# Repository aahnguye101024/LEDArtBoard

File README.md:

# LEDArtBoard
This project is an ESP32 that can control a huge array of leds in order to generate pixel art. With a single 12V input, you can power on an ESP32 and huge array of leds (at very low current draw for each led). It was intended as a gift for a friend, where I could upload an array of values with specific RGB codes to display that color in that specific led location on the array. It was also to test JLCPCB's new at the time feature to assemble PCBs for a super low cost.

# Main Board

# LED Board

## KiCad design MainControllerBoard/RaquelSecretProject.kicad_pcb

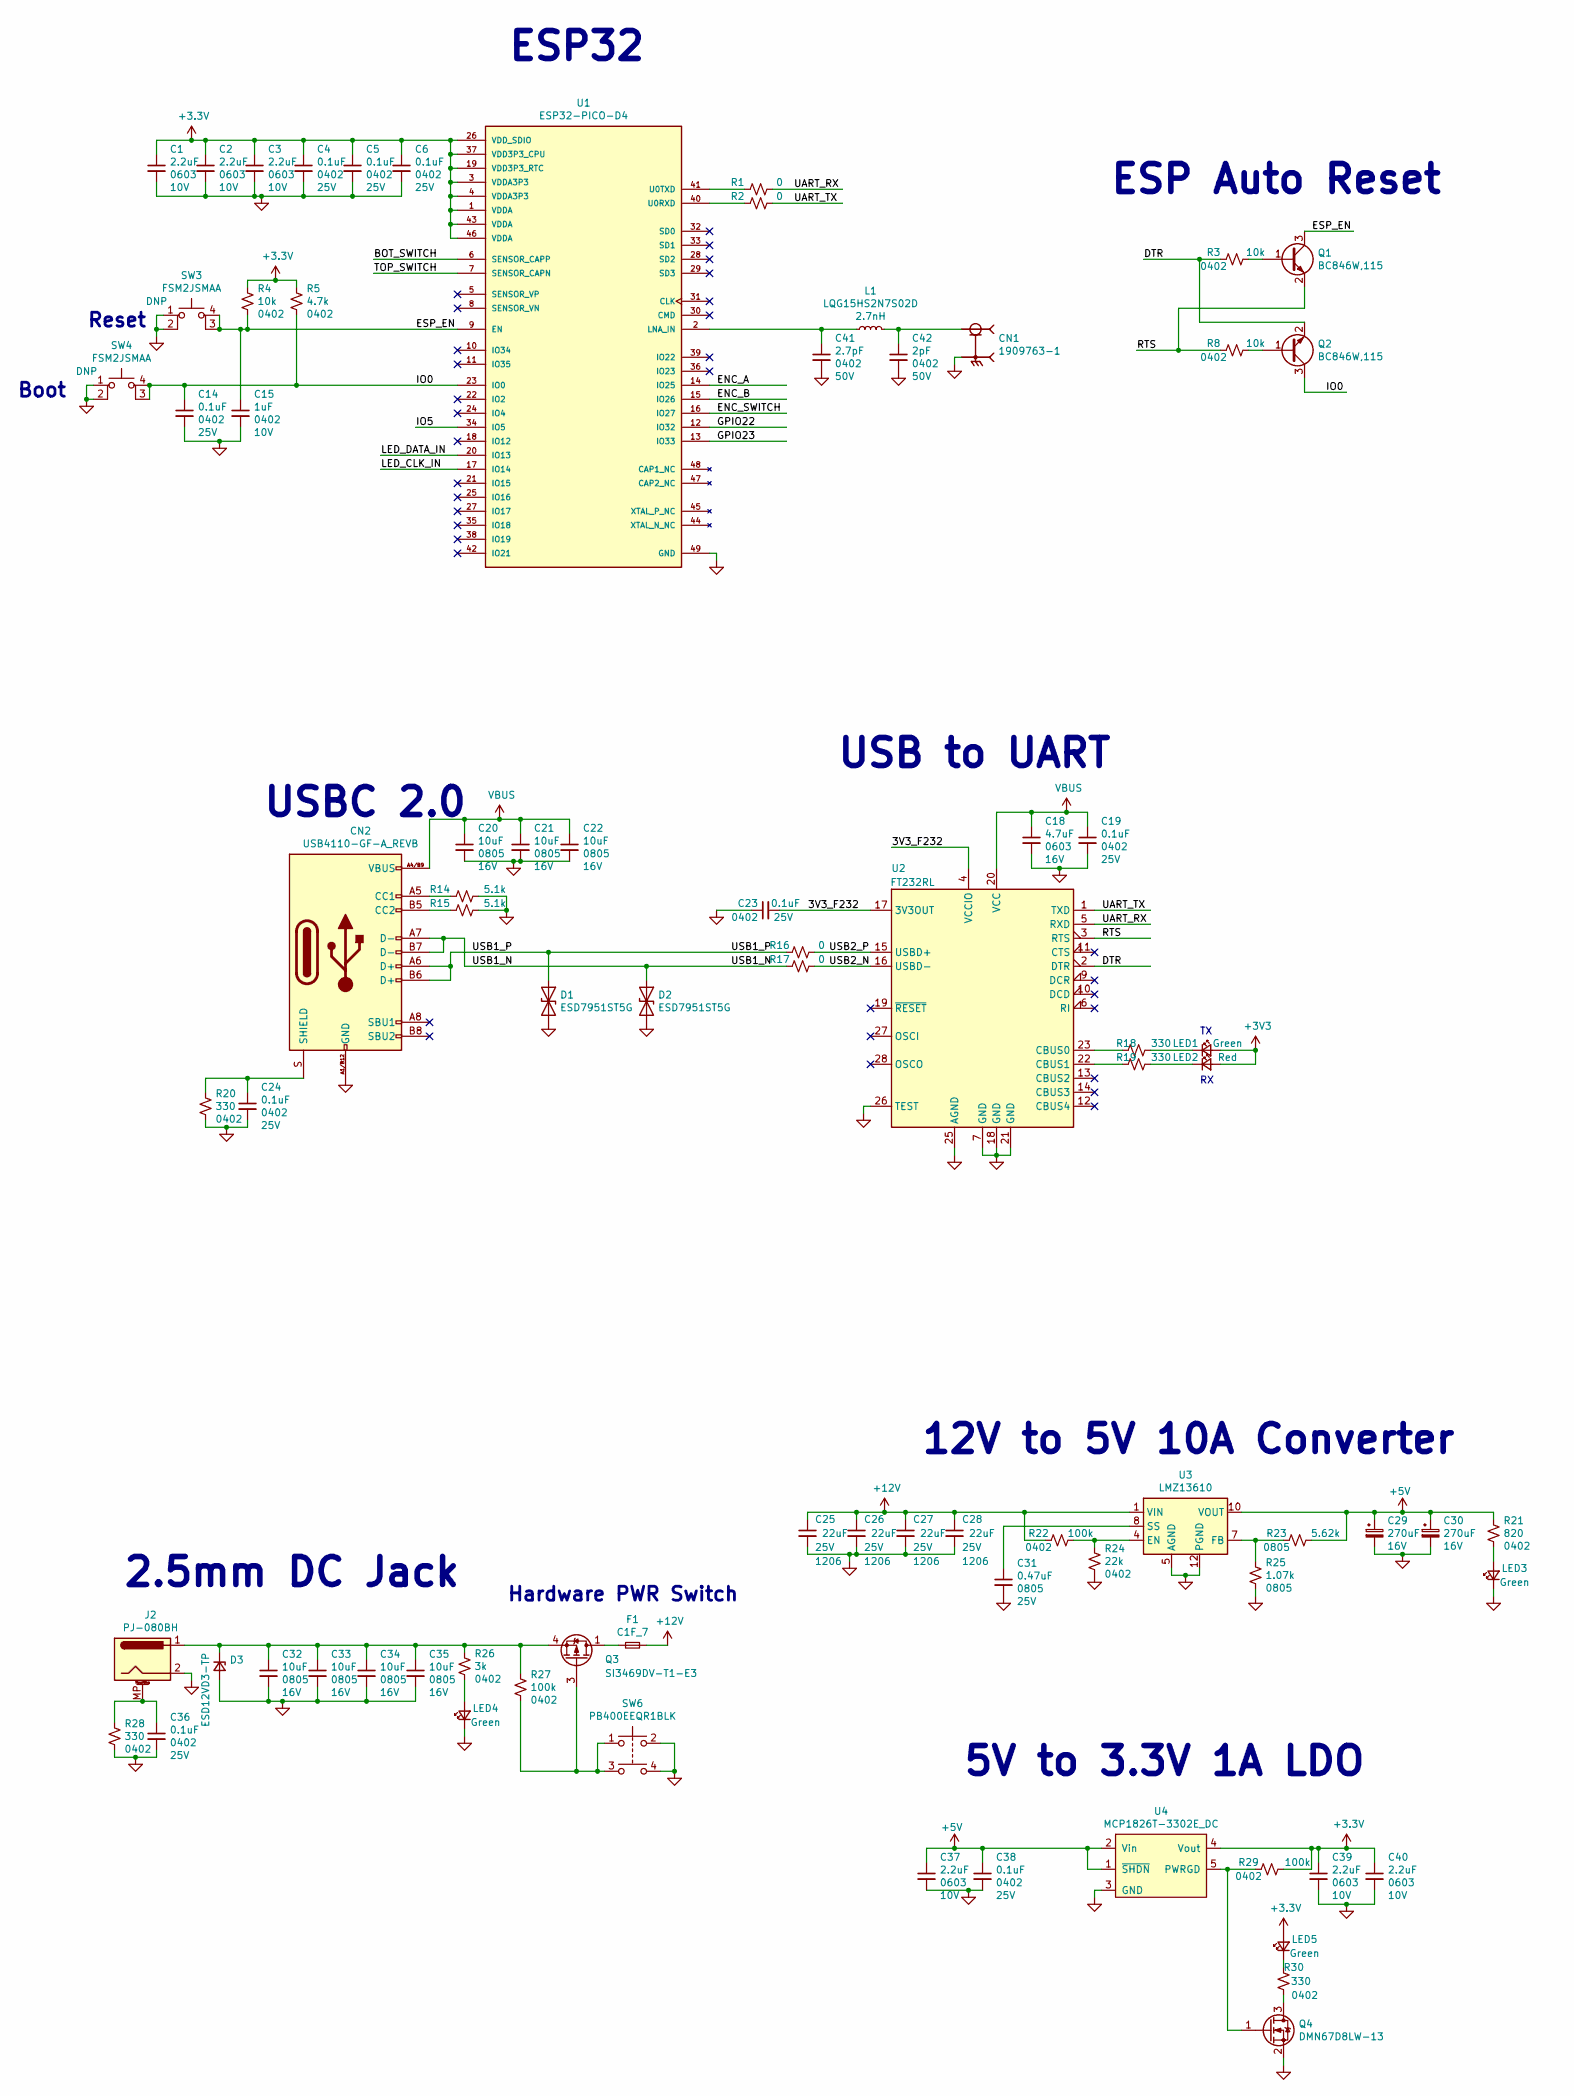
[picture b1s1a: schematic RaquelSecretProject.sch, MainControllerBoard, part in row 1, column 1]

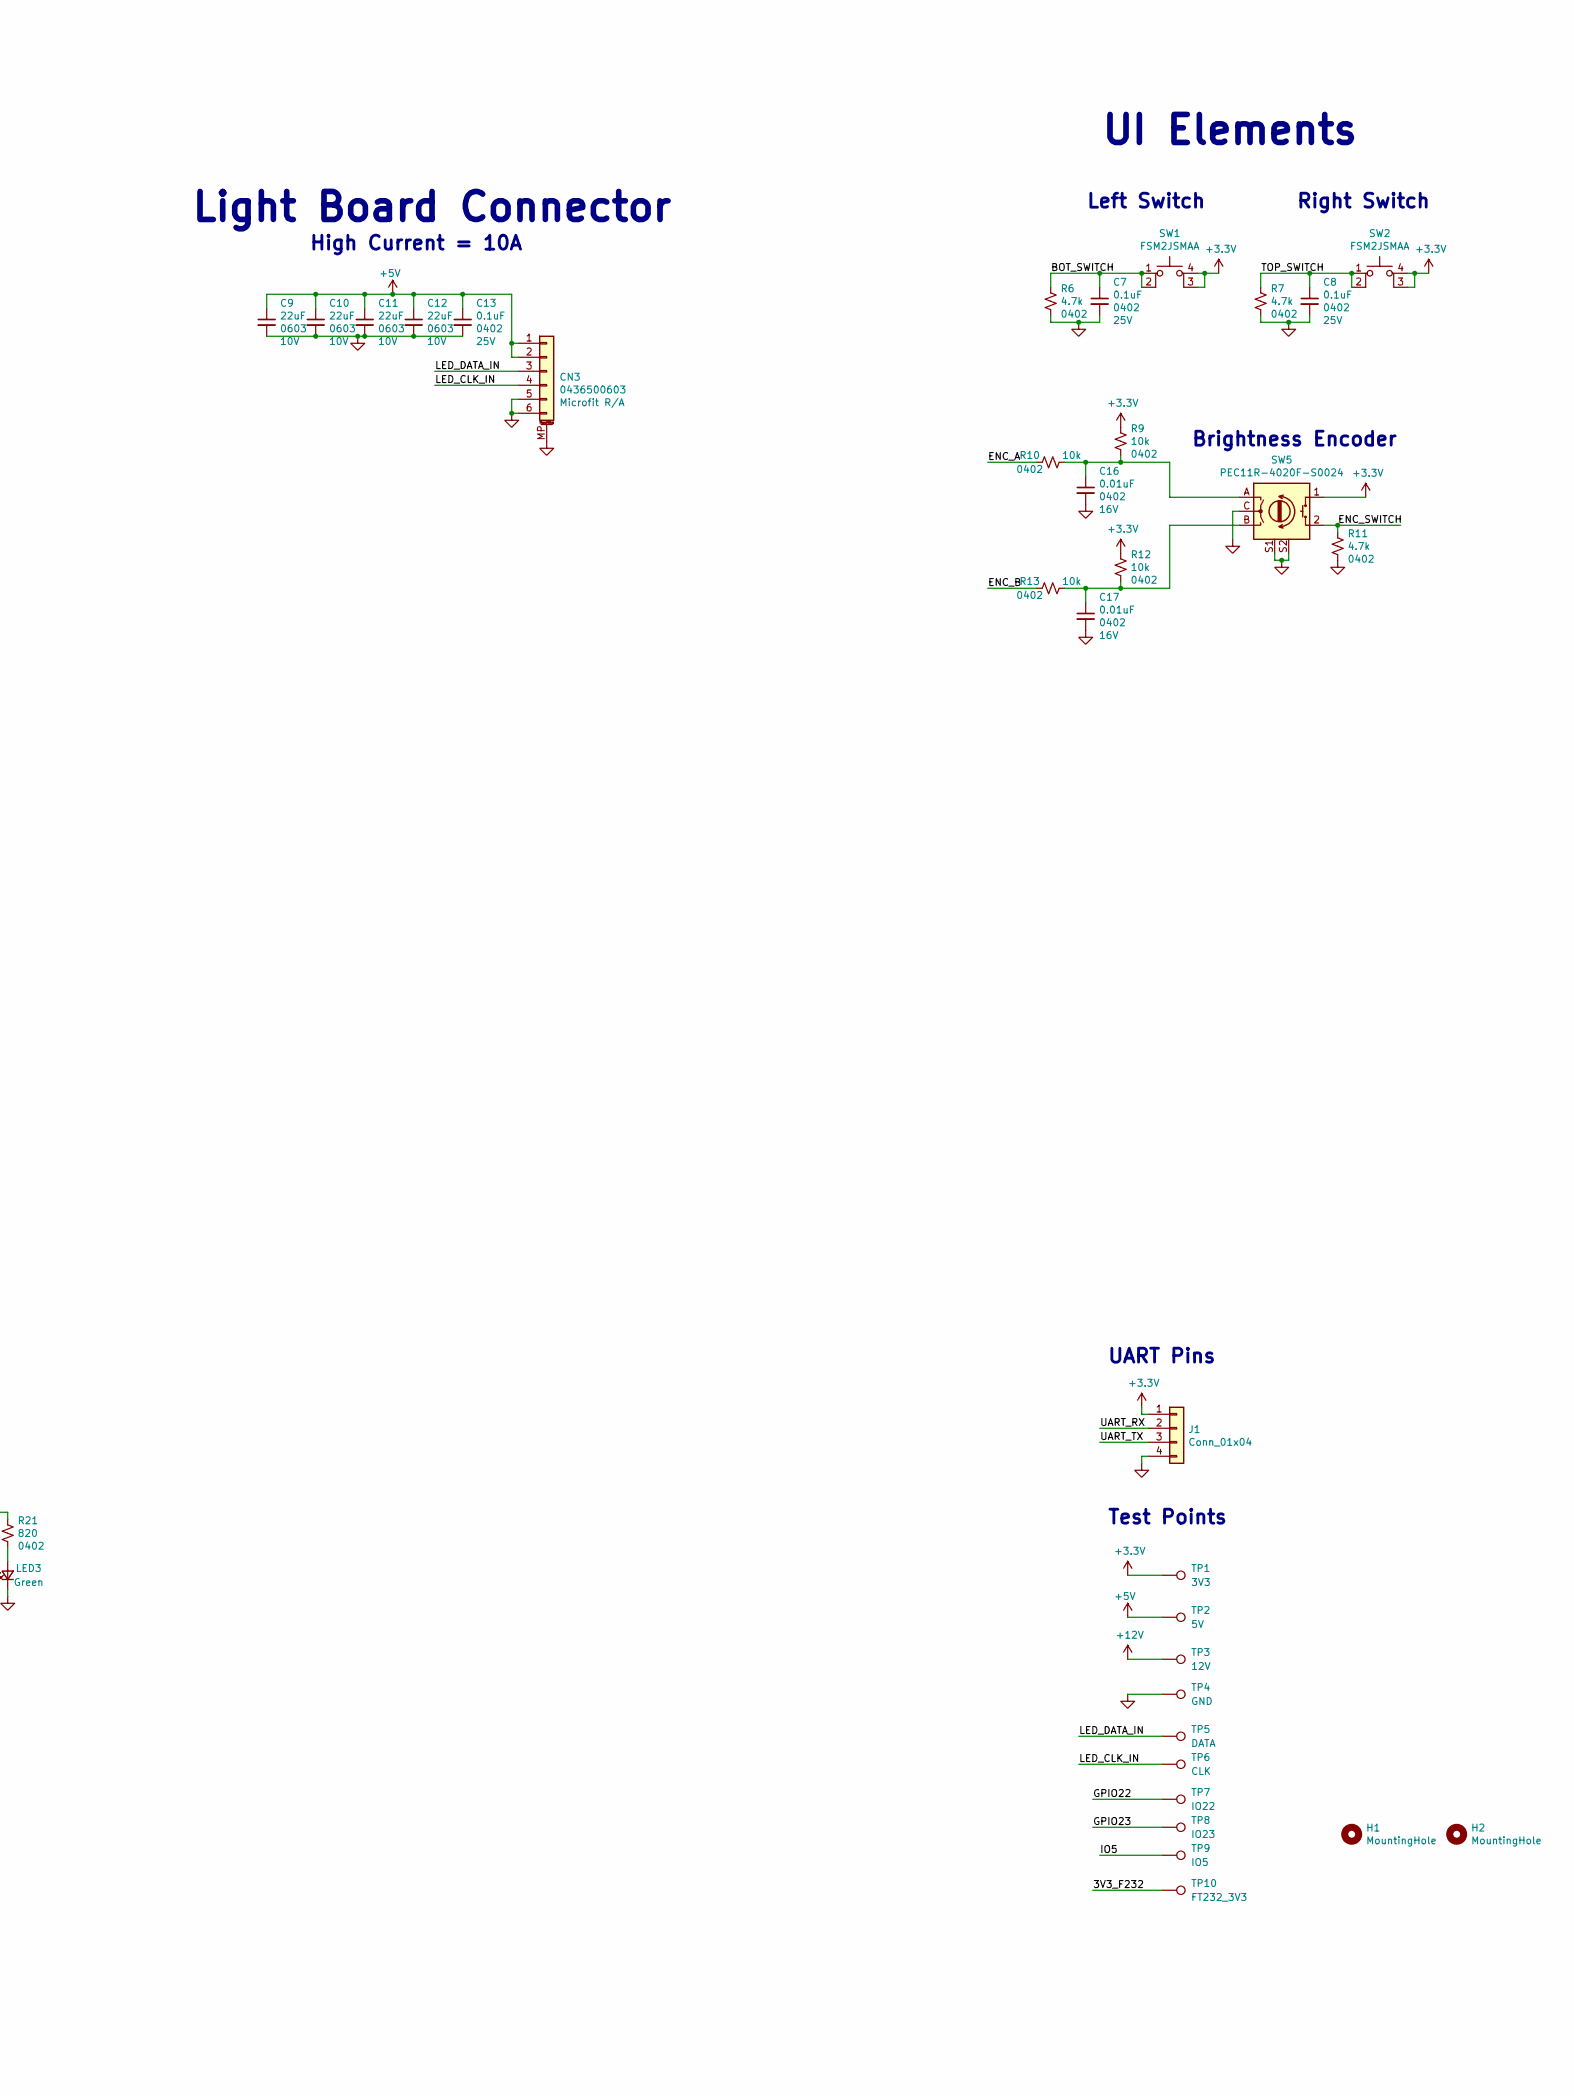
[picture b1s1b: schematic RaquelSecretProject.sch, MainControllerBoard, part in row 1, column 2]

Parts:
C1, C2, C3, C37, C39, C40: 2.2uF; C_0603_1608Metric; Voltage 10V; Part Number 1276-1085-1-ND
C4, C5, C6, C7, C8, C13, C14, C19, C23, C24, C36, C38: 0.1uF; C_0402_1005Metric; Voltage 25V; Part Number 1276-1043-1-ND
C9, C10, C11, C12: 22uF; C_0603_1608Metric; Voltage 10V; Part Number 1276-1274-1-ND
C15: 1uF; C_0402_1005Metric; Voltage 10V; Part Number 1276-1076-1-ND
C16, C17: 0.01uF; C_0402_1005Metric; Voltage 16V; Part Number 478-0402YD103KAT2ACT-ND
C18: 4.7uF; C_0603_1608Metric; Voltage 16V; Part Number 1276-1784-1-ND
C20, C21, C22, C32, C33, C34, C35: 10uF; C_0805_2012Metric; Voltage 16V; Part Number 1276-2893-1-ND
C25, C26, C27, C28: 22uF_1206; C_1206_3216Metric; Voltage 25V; Part Number 1276-3047-1-ND
C29, C30: 270uF; CAP_16SVPG270M; Voltage 16V; Part Number PCE5081CT-ND
C31: 0.47uF; C_0805_2012Metric; Voltage 25V; Part Number 1276-1074-1-ND
C41: 2.7pF; C_0402_1005Metric; Voltage 50V; Part Number 311-1005-1-ND
C42: 2pF; C_0402_1005Metric; Voltage 50V; Part Number 311-1006-1-ND
CN1: 1909763-1; TE_1909763-1; Part Number A118077CT-ND
CN2: USB4110-GF-A_REVB; GCT_USB4110-GF-A_REVB; Part Number 2073-USB4110-GF-A-1-ND
CN3: 0436500603; 436500603; Part Number WM1874-ND
D1, D2: ESD7951ST5G; D_SOD-923; Part Number ESD7951ST5GOSCT-ND
D3: ESD12VD3-TP; D_SOD-323; Part Number ESD12VD3-TPMSCT-ND
F1: C1F_7; Fuse_1206_3216Metric; Part Number 507-1888-1-ND
H1, H2: MountingHole; MountingHole_3.2mm_M3_ISO7380
J1: Conn_01x04; PinHeader_1x04_P2.54mm_Vertical
J2: PJ-080BH; CUI_PJ-080BH; Part Number CP-080BHCT-ND
L1: LQG15HS2N7S02D; L_0402_1005Metric; Part Number 490-2615-1-ND
LED1, LED3, LED4, LED5: SML-D12P8WT86; LED_0603_1608Metric; Part Number 511-1579-1-ND
LED2: SML-D12U1WT86; LED_0603_1608Metric; Part Number SML-D12U1WT86CT-ND
Q1, Q2: BC846W,115; SOT-323_SC-70; Part Number 1727-4850-1-ND
Q3: SI3469DV-T1-E3; TSOT-23-6; Part Number SI3469DV-T1-E3CT-ND
Q4: DMN67D8LW-13; SOT-323_SC-70; Part Number DMN67D8LW-13DICT-ND
R1, R2, R16, R17: 0; R_0402_1005Metric; Part Number RMCF0402ZT0R00CT-ND
R3, R4, R8, R9, R10, R12, R13: 10k; R_0402_1005Metric; Part Number RMCF0402FT10K0CT-ND
R5, R6, R7, R11: 4.7k; R_0402_1005Metric; Part Number RMCF0402FT4K70CT-ND
R14, R15: 5.1k; R_0402_1005Metric; Part Number 311-5.10KLRCT-ND
R18, R19, R20, R28, R30: 330; R_0402_1005Metric; Part Number 311-330LRCT-ND
R21: 820; R_0402_1005Metric; Part Number RMCF0402FT820RCT-ND
R22, R27, R29: 100k; R_0402_1005Metric; Part Number 2037-PFR05S-104-FNHCT-ND
R23: 5.62k; R_0805_2012Metric; Part Number RMCF0805FT5K62CT-ND
R24: 22k; R_0402_1005Metric; Part Number CR0402-FX-2202GLFCT-ND
R25: 1.07k; R_0805_2012Metric; Part Number 311-1.07KCRCT-ND
R26: 3k; R_0402_1005Metric; Part Number RMCF0402FT3K00CT-ND
SW1, SW2, SW3, SW4: FSM2JSMAA; SW_2-1437565-8; Part Number 450-3355-ND
SW5: PEC11R-4020F-S0024; Part Number PEC11R-4020F-S0024-ND
SW6: PB400EEQR1BLK; Part Number Ologic
TP1: 3V3; CurrentTestPoint
TP2: 5V; CurrentTestPoint
TP3: 12V; CurrentTestPoint
TP4: GND; CurrentTestPoint
TP5: DATA; CurrentTestPoint
TP6: CLK; CurrentTestPoint
TP7: IO22; CurrentTestPoint
TP8: IO23; CurrentTestPoint
TP9: IO5; CurrentTestPoint
TP10: FT232_3V3; CurrentTestPoint
U1: ESP32-PICO-D4; QFN-48-1EP_7x7mm_P0.5mm_EP5.3x5.3mm_ThermalVias; Part Number 1904-1029-1-ND
U2: FT232RL; SSOP-28_5.3x10.2mm_P0.65mm; Part Number Ologic
U3: LMZ13610; Texas_NDY0011A; Part Number Ologic
U4: MCP1826T-3302E_DC; SOT-223-6_TabPin3; Part Number Ologic

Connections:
+5V: C9.1, C10.1, C11.1, C12.1, C13.1, C29.1, C30.1, C37.1, C38.1, CN3.1, CN3.2, R21.1, R23.1, TP2.1, U3.10 (VOUT), U3.11 (VOUT), U4.1 (~SHDN~), U4.2 (Vin)
+12V: C25.1, C26.1, C27.1, C28.1, F1.2, R22.2, TP3.1, U3.1 (VIN), U3.2 (VIN)
/3V3_F232: C23.2, TP10.1, U2.4 (VCCIO), U2.17 (3V3OUT)
/BOT_SWITCH: C7.1, R6.1, SW1.1, SW1.2, U1.6 (SENSOR_CAPP)
/DTR: Q2.2 (E), R3.2, U2.2 (DTR)
/ENC_A: R10.2, U1.14 (IO25)
/ENC_B: R13.2, U1.15 (IO26)
/ENC_SWITCH: R11.1, SW5.2, U1.16 (IO27)
/ESP_EN: C15.1, Q1.3 (C), R4.2, SW3.3 (K), SW3.4 (A), U1.9 (EN)
/GPIO22: TP7.1, U1.12 (IO32)
/GPIO23: TP8.1, U1.13 (IO33)
/IO0: C14.1, Q2.3 (C), R5.2, SW4.3 (K), SW4.4 (A), U1.23 (IO0)
/IO5: TP9.1, U1.34 (IO5)
/LED_CLK_IN: CN3.4, TP6.1, U1.17 (IO14)
/LED_DATA_IN: CN3.3, TP5.1, U1.20 (IO13)
/RTS: Q1.2 (E), R8.2, U2.3 (RTS)
/TOP_SWITCH: C8.1, R7.1, SW2.1, SW2.2, U1.7 (SENSOR_CAPN)
/UART_RX: J1.2, R1.1, U2.5 (RXD)
/UART_TX: J1.3, R2.1, U2.1 (TXD)
/USB1_N: CN2.A7 (D-), CN2.B7 (D-), D2.1 (A1), R17.2
/USB1_P: CN2.A6 (D+), CN2.B6 (D+), D1.1 (A1), R16.2
/USB2_N: R17.1, U2.16 (USBD-)
/USB2_P: R16.1, U2.15 (USBD+)
GND: C1.2, C2.2, C3.2, C4.2, C5.2, C6.2, C7.2, C8.2, C9.2, C10.2, C11.2, C12.2, C13.2, C14.2, C15.2, C16.2, C17.2, C18.2, C19.2, C20.2, C21.2, C22.2, C23.1, C24.2, C25.2, C26.2, C27.2, C28.2, C29.2, C30.2, C31.2, C32.2, C33.2, C34.2, C35.2, C36.2, C37.2, C38.2, C39.2, C40.2, C41.2, C42.2, CN1.2, CN1.3, CN2.A1/B12 (GND), CN2.B1/A12 (GND), CN3.5, CN3.6, CN3.MP (MountPin), D1.2 (A2), D2.2 (A2), D3.2 (A), J1.4, J2.2, LED3.1 (K), LED4.1 (K), Q4.2 (S), R6.2, R7.2, R11.2, R14.2, R15.2, R20.2, R24.2, R25.2, R28.2, SW3.1, SW3.2, SW4.1, SW4.2, SW5.C, SW5.S1 (Shield), SW5.S2 (Shield), SW6.2, SW6.4, TP4.1, U1.49 (GND), U2.7 (GND), U2.18 (GND), U2.21 (GND), U2.25 (AGND), U2.26 (TEST), U3.3 (AGND), U3.5 (AGND), U3.6 (AGND), U3.12 (PGND), U4.3 (GND)
unnamed: C16.1, R9.2, R10.1, SW5.A
unnamed: C17.1, R12.2, R13.1, SW5.B
unnamed: C24.1, CN2.S (SHIELD), R20.1
unnamed: C31.1, U3.8 (SS)
unnamed: C32.1, C33.1, C34.1, C35.1, D3.1 (K), J2.1, Q3.4 (S), R26.1, R27.1
unnamed: C36.1, J2.MP (MountPin), R28.1
unnamed: C41.1, L1.1, U1.2 (LNA_IN)
unnamed: C42.1, CN1.1, L1.2
unnamed: CN2.A5 (CC1), R14.1
unnamed: CN2.B5 (CC2), R15.1
unnamed: F1.1, Q3.1 (D), Q3.2 (D), Q3.5 (D), Q3.6 (D)
unnamed: LED1.1 (K), R18.1
unnamed: LED2.1 (K), R19.1
unnamed: LED3.2 (A), R21.2
unnamed: LED4.2 (A), R26.2
unnamed: LED5.1 (K), R30.2
unnamed: Q1.1 (B), R3.1
unnamed: Q2.1 (B), R8.1
unnamed: Q3.3 (G), R27.2, SW6.1, SW6.3
unnamed: Q4.1 (G), R29.1, U4.5 (PWRGD)
unnamed: Q4.3 (D), R30.1
unnamed: R1.2, U1.41 (U0TXD)
unnamed: R2.2, U1.40 (U0RXD)
unnamed: R18.2, U2.23 (CBUS0)
unnamed: R19.2, U2.22 (CBUS1)
unnamed: R22.1, R24.1, U3.4 (EN)
unnamed: R23.2, R25.1, U3.7 (FB)
VBUS: C18.1, C19.1, C20.1, C21.1, C22.1, CN2.A4/B9 (VBUS), CN2.B4/A9 (VBUS), U2.20 (VCC)

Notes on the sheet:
USB to UART
USBC 2.0
ESP32
12V to 5V 10A Converter
5V to 3.3V 1A LDO
2.5mm DC Jack
ESP Auto Reset
Reset
Boot
Brightness Encoder
Left Switch
Right Switch
Light Board Connector
High Current = 10A
Hardware PWR Switch
Test Points
UART Pins
UI Elements

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
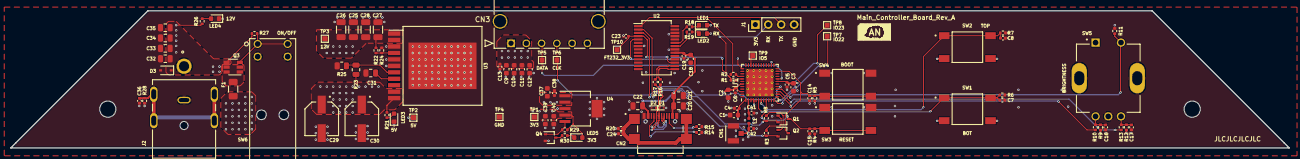
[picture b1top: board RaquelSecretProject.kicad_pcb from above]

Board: 4 copper layers, 251.2 x 26.9 mm, 113 parts (0 on the bottom side), 53 nets.

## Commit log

2024-01-31 initial Push
2024-01-31 Updated read me
2024-01-31 Fixed read me

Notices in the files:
parts and their libraries:
Copyright 2021 Accelerated Designs. All rights reserved.
